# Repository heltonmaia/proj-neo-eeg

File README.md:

# Neo-EEG Project

Open-source 8-channel EEG acquisition system based on ADS1299 and ESP32.

## Hardware

| Component | Description |
|-----------|-------------|
| MCU | ESP32 |
| ADC | ADS1299 (8 channels, 24-bit) |
| Connection | WiFi (UDP) or Bluetooth SPP |
| PCB | PotyEEG v9 |

## Project Structure

```
proj-neo-eeg/
├── docs/
│   ├── datasheets/             # ADS1299 datasheets
│   └── troubleshooting.md      # Troubleshooting guide
│
├── firmware/
│   ├── esp32-wifi/             # ESP32 WiFi firmware
│   │   └── EEG_Poty_ESP32_V10/
│   └── libraries/              # Arduino dependencies
│
├── hardware/
│   └── pcb/
│       └── PotyEEG_v9/         # Eagle PCB files
│
├── software-web/               # Web application (recommended)
│   ├── run.py                  # Cross-platform launcher
│   ├── backend/                # FastAPI server
│   └── frontend/               # React application
│
└── software-processing/        # OpenBCI GUI (legacy)
    └── openbci-gui/
```

## Quick Start (Web Application)

### 1. Flash Firmware

1. Open Arduino IDE
2. Install ESP32 board support
3. Open `firmware/esp32-wifi/EEG_Poty_ESP32_V10/EEG_Poty_ESP32_V10.ino`
4. Select board: ESP32 Dev Module
5. Upload

### 2. Connect to ESP32 WiFi

- **SSID:** `Potyplex-EEG`
- **Password:** `eeg12345`

### 3. Run Web Application

```bash
cd software-web
python run.py
```

Select option `1` to start all services, then open http://localhost:3000

### 4. Use

1. Click **Start** to begin EEG streaming
2. Click **Start Camera** to enable video (optional)
3. Select **Signals** and/or **Video** checkboxes
4. Click **REC** to record

## Features

- Real-time 8-channel EEG visualization
- USB camera streaming
- Recording to CSV (signals) and MP4 (video)
- Offline recording playback
- Dark/Light theme
- Channel selection and zoom controls
- Cross-platform (Linux, Windows, macOS)

## Firmware

The ESP32 firmware streams OpenBCI-compatible packets:

- **Protocol**: OpenBCI binary format (33 bytes)
- **Sample Rate**: 250 Hz
- **Channels**: 8 (ADS1299)
- **Transport**: UDP over WiFi

## Requirements

### Firmware
- Arduino IDE 2.x
- ESP32 Board Support

### Web Application
- Python 3.8+
- Node.js 18+
- OpenCV (for camera)

## License

MIT License

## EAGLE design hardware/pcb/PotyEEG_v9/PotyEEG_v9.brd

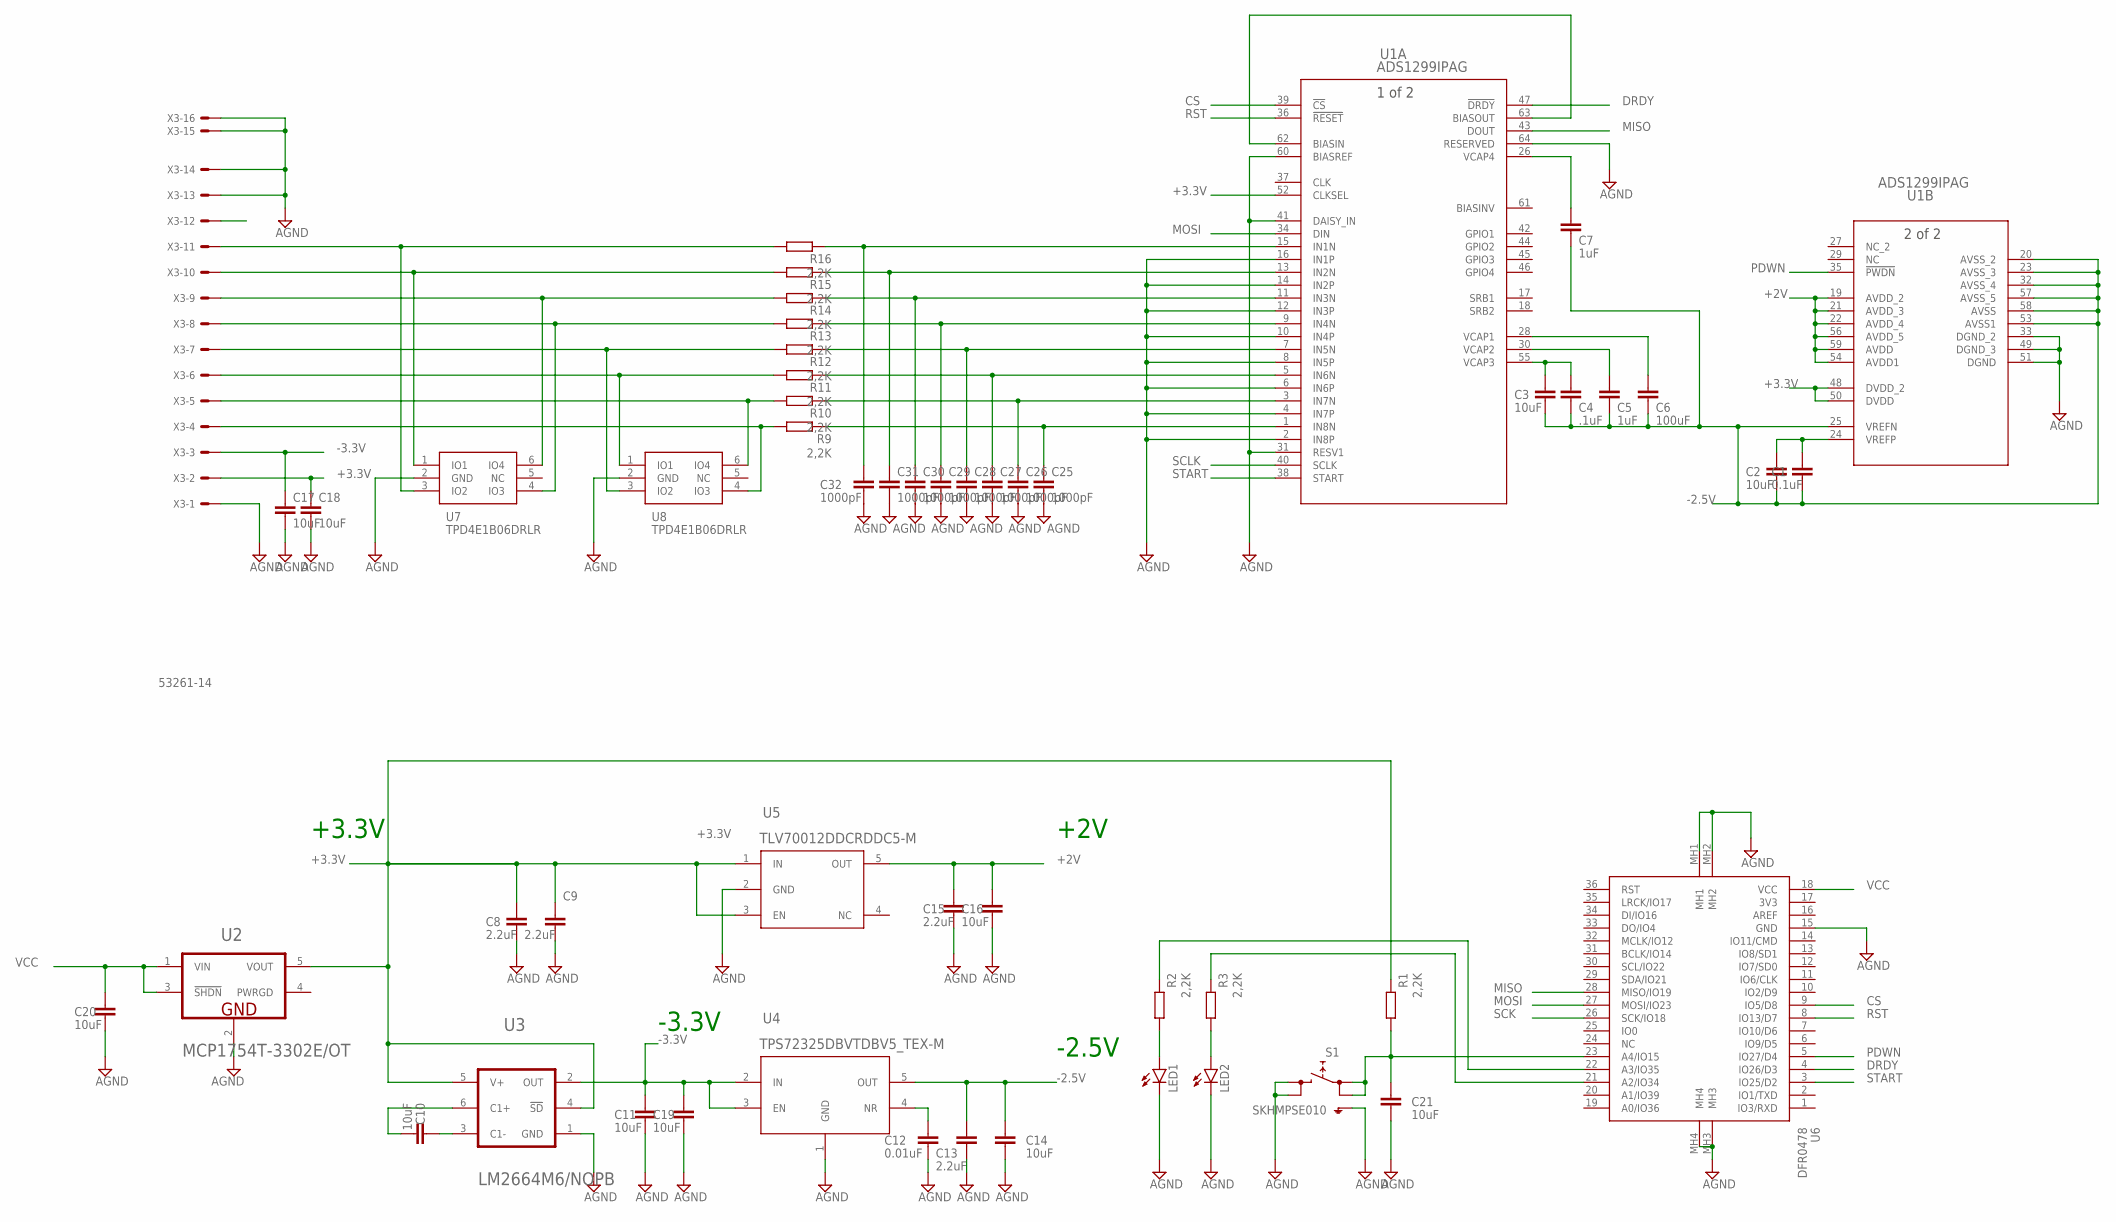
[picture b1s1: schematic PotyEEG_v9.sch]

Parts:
C1: 0.1uF; C0805K
C2, C3, C10, C11, C14, C16, C19, C20, C21: 10uF; C0805K
C4: .1uF; C0805K
C5, C7: 1uF; C0805K
C6: 100uF; C0805K
C8, C9, C13, C15: 2.2uF; C0805K
C12: 0.01uF; C0805K
C17, C18: 10uF; C0603
C25, C26, C27, C28, C29, C30, C31, C32: 1000pF; C0603
LED1, LED2: LEDSML0805; SML0805
R1, R2, R3, R9, R10, R11, R12, R13, R14, R15, R16: 2,2K; R0603
S1: SKHMPSE010; SKHMPXE010
U1: ADS1299IPAG; PAG64_TEX
U2: MICROCHIP_MCP1754T-3302E-OTMICROCHIP_MCP1754T-330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; MICROCHIP_MCP1754T-3302E-OT_1
U3: TEXAS_INSTRUMENTS_LM2664M6-NOPBTEXAS_INSTRUMENTS_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; TEXAS_INSTRUMENTS_LM2664M6-NOPB_2
U4: TPS72325DBVTDBV5_TEX-M; DBV5_TEX-M
U5: TLV70012DDCRDDC5-M; DDC5-M
U6: DFR0478; FIREBEETLE_ESP32
U7, U8: TPD4E1B06DRLR; SOP50P160X60-6N
X3: 53261-14

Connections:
+2V: C15.1, C16.1, U1.19 (AVDD_2), U1.21 (AVDD_3), U1.22 (AVDD_4), U1.54 (AVDD1), U1.56 (AVDD_5), U1.59 (AVDD), U5.5 (OUT)
+3.3V: C8.1, C9.1, C18.1, R1.1, U1.48 (DVDD_2), U1.50 (DVDD), U1.52 (CLKSEL), U2.5 (VOUT), U3.4 (!SD!), U3.5 (V+), U5.1 (IN), U5.3 (EN), X3.2
-2.5V: C1.2, C2.2, C3.2, C4.2, C5.2, C6.2, C7.2, C13.1, C14.1, U1.20 (AVSS_2), U1.23 (AVSS_3), U1.25 (VREFN), U1.32 (AVSS_4), U1.53 (AVSS1), U1.57 (AVSS_5), U1.58 (AVSS), U4.5 (OUT)
-3.3V: C11.1, C17.1, C19.1, U3.2 (OUT), U4.2 (IN), U4.3 (EN), X3.3
CS: U1.39 (!CS), U6.9 (IO5/D8)
DRDY: U1.47 (!DRDY), U6.4 (IO26/D3)
GND: C8.2, C9.2, C11.2, C12.2, C13.2, C14.2, C15.2, C16.2, C17.2, C18.2, C19.2, C20.2, C21.2, C25.2, C26.2, C27.2, C28.2, C29.2, C30.2, C31.2, C32.2, LED1.C, LED2.C, S1.3 (2.1), S1.4 (2.2), S1.5 (SH), U1.2 (IN8P), U1.4 (IN7P), U1.6 (IN6P), U1.8 (IN5P), U1.10 (IN4P), U1.12 (IN3P), U1.14 (IN2P), U1.16 (IN1P), U1.31 (RESV1), U1.33 (DGND_2), U1.41 (DAISY_IN), U1.49 (DGND_3), U1.51 (DGND), U1.60 (BIASREF), U1.64 (RESERVED), U2.2 (GND), U3.1 (GND), U4.1 (GND), U5.2 (GND), U6.15 (GND), U6.MH1, U6.MH2, U6.MH3, U6.MH4, U7.2 (GND), U8.2 (GND), X3.1, X3.13, X3.14, X3.S1, X3.S2
MISO: U1.43 (DOUT), U6.28 (MISO/IO19)
MOSI: U1.34 (DIN), U6.27 (MOSI/IO23)
unnamed: C1.1, C2.1, U1.24 (VREFP)
unnamed: C3.1, C4.1, U1.55 (VCAP3)
unnamed: C5.1, U1.30 (VCAP2)
unnamed: C6.1, U1.28 (VCAP1)
unnamed: C7.1, U1.26 (VCAP4)
unnamed: C21.1, R1.2, S1.1 (1.1), S1.2 (1.2), U6.23 (A4/IO15)
unnamed: R9.2, U8.4 (IO3), X3.4
unnamed: R10.2, U8.6 (IO4), X3.5
unnamed: R11.2, U8.1 (IO1), X3.6
unnamed: R2.1, U6.22 (A3/IO35)
unnamed: R12.2, U8.3 (IO2), X3.7
unnamed: C12.1, U4.4 (NR)
unnamed: R13.2, U7.4 (IO3), X3.8
unnamed: C10.1, U3.3 (C1-)
unnamed: C10.2, U3.6 (C1+)
unnamed: R14.2, U7.6 (IO4), X3.9
unnamed: LED1.A, R2.2
unnamed: R15.2, U7.1 (IO1), X3.10
unnamed: U1.62 (BIASIN), U1.63 (BIASOUT)
unnamed: R3.1, U6.21 (A2/IO34)
unnamed: LED2.A, R3.2
unnamed: C25.1, R9.1, U1.1 (IN8N)
unnamed: C26.1, R10.1, U1.3 (IN7N)
unnamed: C27.1, R11.1, U1.5 (IN6N)
unnamed: C28.1, R12.1, U1.7 (IN5N)
unnamed: C29.1, R13.1, U1.9 (IN4N)
unnamed: C30.1, R14.1, U1.11 (IN3N)
unnamed: C31.1, R15.1, U1.13 (IN2N)
unnamed: C32.1, R16.1, U1.15 (IN1N)
unnamed: R16.2, U7.3 (IO2), X3.11
PDWN: U1.35 (!PWDN), U6.5 (IO27/D4)
RST: U1.36 (!RESET), U6.8 (IO13/D7)
SCK: U6.26 (SCK/IO18)
SCLK: U1.40 (SCLK)
START: U1.38 (START), U6.3 (IO25/D2)
VCC: C20.1, U2.1 (VIN), U2.3 (!SHDN!), U6.18 (VCC)

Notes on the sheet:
+3.3V
-3.3V
-2.5V
+2V

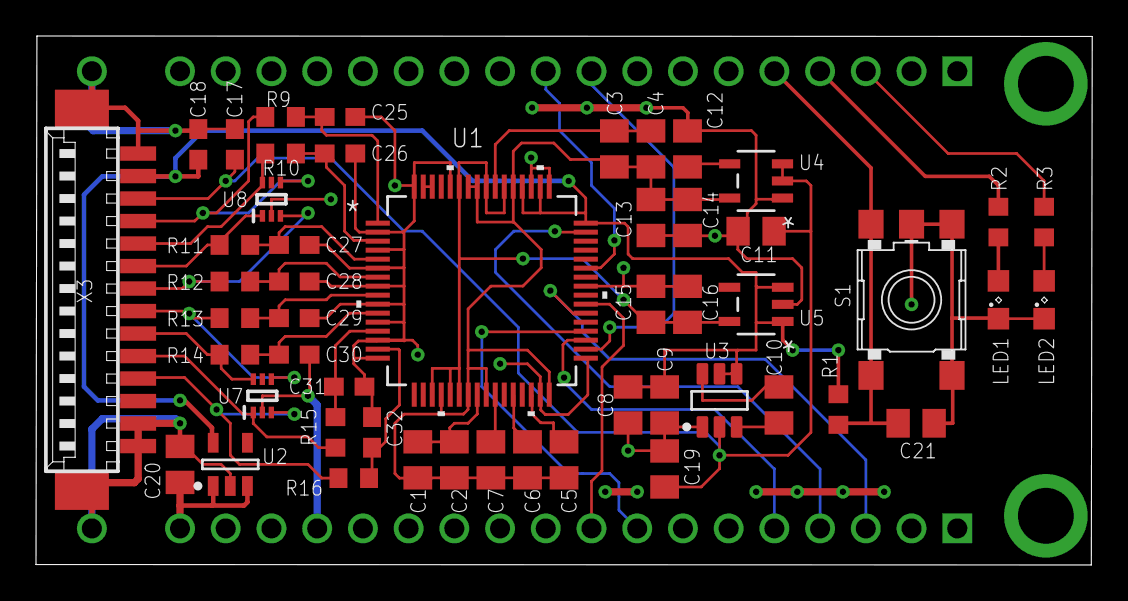
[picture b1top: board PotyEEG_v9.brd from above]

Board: 2 copper layers, 58.7 x 29.4 mm, 52 parts (1 on the bottom side), 43 nets.

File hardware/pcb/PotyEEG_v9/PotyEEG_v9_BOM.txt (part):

Partlist exported from D:/Users/WinU31/Documents/Projects/PotyEEG/Project/Hardware/PotyEEG_v9.sch at 29/10/2021 20:17

Part Value                                                              Device                                                             Package                           Description                                                   
C1   0.1uF                                                              C-EUC0805K                                                         C0805K                            CAPACITOR, European symbol                                    
C2   10uF                                                               C-EUC0805K                                                         C0805K                            CAPACITOR, European symbol                                    
C3   10uF                                                               C-EUC0805K                                                         C0805K                            CAPACITOR, European symbol                                    
C4   .1uF                                                               C-EUC0805K                                                         C0805K                            CAPACITOR, European symbol                                    
C5   1uF                                                                C-EUC0805K                                                         C0805K                            CAPACITOR, European symbol                                    
C6   100uF                                                              C-EUC0805K                                                         C0805K                            CAPACITOR, European symbol                                    
C7   1uF                                                                C-EUC0805K                                                         C0805K                            CAPACITOR, European symbol                                    
C8   2.2uF                                                              C-EUC0805K                                                         C0805K                            CAPACITOR, European symbol                                    
C9   2.2uF                                                              C-EUC0805K                                                         C0805K                            CAPACITOR, European symbol                                    
C10  10uF                                                               C-EUC0805K                                                         C0805K                            CAPACITOR, European symbol                                    
C11  10uF                                                               C-EUC0805K                                                         C0805K                            CAPACITOR, European symbol                                    
C12  0.01uF                                                             C-EUC0805K                                                         C0805K                            CAPACITOR, European symbol                                    
C13  2.2uF                                                              C-EUC0805K                                                         C0805K                            CAPACITOR, European symbol                                    
C14  10uF                                                               C-EUC0805K                                                         C0805K                            CAPACITOR, European symbol                                    
C15  2.2uF                                                              C-EUC0805K                                                         C0805K                            CAPACITOR, European symbol                                    
C16  10uF                                                               C-EUC0805K                                                         C0805K                            CAPACITOR, European symbol                                    
C17  10uF                                                               C-EUC0603                                                          C0603                             CAPACITOR, European symbol                                    
C18  10uF                                                               C-EUC0603                                                          C0603                             CAPACITOR, European symbol                                    
C19  10uF                                                               C-EUC0805K                                                         C0805K                            CAPACITOR, European symbol                                    
C20  10uF                                                               C-EUC0805K                                                         C0805K                            CAPACITOR, European symbol                                    
C21  10uF                                                               C-EUC0805K                                                         C0805K                            CAPACITOR, European symbol                                    
C25  1000pF                                                             C-EUC0603                                                          C0603                             CAPACITOR, European symbol                                    
C26  1000pF                                                             C-EUC0603                                                          C0603                             CAPACITOR, European symbol                                    
C27  1000pF                                                             C-EUC0603                                                          C0603                             CAPACITOR, European symbol                                    
C28  1000pF                                                             C-EUC0603                                                          C0603                             CAPACITOR, European symbol                                    
C29  1000pF                                                             C-EUC0603                                                          C0603                             CAPACITOR, European symbol                                    
C30  1000pF                                                             C-EUC0603                                                          C0603                             CAPACITOR, European symbol                                    
C31  1000pF                                                             C-EUC0603                                                          C0603                             CAPACITOR, European symbol                                    
C32  1000pF                                                             C-EUC0603                                                          C0603                             CAPACITOR, European symbol                                    
LED1                                                                    LEDSML0805                                                         SML0805                           LED                                                           
LED2                                                                    LEDSML0805                                                         SML0805                           LED                                                           
R1   2,2K                                                               R-EU_R0603                                                         R0603                             RESISTOR, European symbol                                     
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
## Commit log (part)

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2026-02-26 Add initial content to readme.md
2026-02-27 processing libraries and updated readme.md
2026-02-27 Reorganize project and add complete EEG system
    - Add ESP32 firmware (EEG_Poty_ESP32_V10) with Arduino libraries
    - Add PotyEEG v9 PCB files (schematic, board, BOM, Gerber)
    - Add ADS1299 datasheets
    - Add modified OpenBCI GUI with CH340/Bluetooth support
    - Add scripts: connect-bluetooth.sh, open-gui.sh
    - Add documentation and troubleshooting guide
2026-03-01 Add automatic UV environment setup to run.sh
    Features:
    - Check for UV environment on startup
    - Ask user to create in project root or custom location
    - Save configuration to .env.local
    - Show Python env status in menu
    - Add 's' option to re-setup environment
2026-03-01 Auto-detect existing UV environment before asking user
2026-03-01 Fix UDP receiver using native asyncio DatagramProtocol
    - Replace run_in_executor with asyncio.DatagramProtocol
    - Add data queue for decoupled broadcast
    - Separate broadcast worker task
    - Better stats with rate calculation
2026-03-01 Fix streaming stability with batched WebSocket messages
    Backend:
    - Send samples in batches every 50ms (20 batches/sec)
    - Reduces WebSocket overhead from 250 to 20 messages/sec
    - Use shortened JSON keys (s, c, a) for less bandwidth
    - Simple buffer swap instead of deque processing
    Frontend:
2026-03-02 Improve recording controls, UI layout, and video playback
    - Move REC button to right side with Signal/Video checkboxes
    - Record only selected channels, lock selection during recording
    - Move channel selector to side panel below camera
    - Add System Console panel with connection status and event log
    - Add Quick Info panel with stats and indicators
    - Fix camera status callback to update parent component
2026-03-02 Improve recording logic, UI stability, and video playback
    - Remove grid background from EEG charts (live and recordings)
    - Fix ESP32 indicator to show stable text with pulsing dot only
    - Add smooth CSS transitions to prevent UI flickering
    - Separate camera and signal controls (independent start/stop)
    - Fix recording checkboxes to use streaming state (more stable)
    - Disable Stop buttons during active recording to prevent data loss
2026-03-02 Add backend tests, record directly to MP4, update docs
    - Add 20 backend tests (packet parser, API endpoints, recording, WebSocket)
    - Record video directly to MP4 (mp4v codec) instead of AVI
    - Remove ffmpeg conversion dependency for video playback
    - Add test option (t) to run.sh menu
    - Update CLAUDE.md, README.md with current features and test instructions
2026-03-03 Replace run.sh with cross-platform run.py
    - Add run.py: single Python script for Linux, Windows, macOS
    - Remove run.sh (bash-only script)
    - Same interactive menu with all features
    - Update documentation for new launcher
2026-03-04 ffmpeg python
